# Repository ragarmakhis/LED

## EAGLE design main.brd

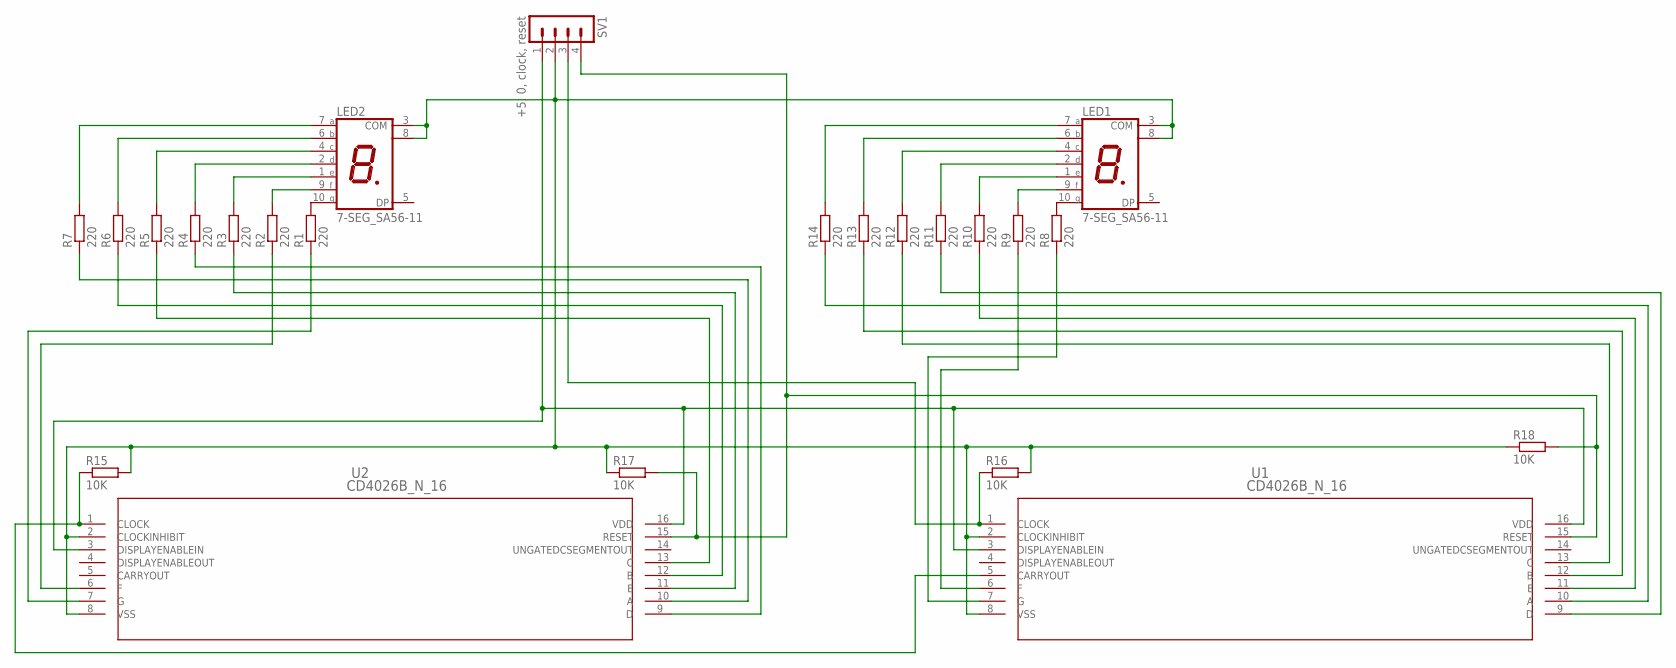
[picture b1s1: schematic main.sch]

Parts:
LED1, LED2: 7-SEG_SA56-11; SA56-11
R1, R2, R3, R4, R5, R6, R7, R8, R9, R10, R11, R12, R13, R14: 220; R0805
R15, R16, R17, R18: 10K; R0805
SV1: +5, 0, clock, reset; MA04-1
U1, U2: CD4026B_N_16; N16

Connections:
unnamed: LED2.10 (G), R1.2
unnamed: LED2.9 (F), R2.2
unnamed: LED2.1 (E), R3.2
unnamed: LED2.2 (D), R4.2
unnamed: LED2.4 (C), R5.2
unnamed: LED2.6 (B), R6.2
unnamed: LED2.7 (A), R7.2
unnamed: SV1.1, U1.3 (DISPLAYENABLEIN), U1.16 (VDD), U2.3 (DISPLAYENABLEIN), U2.16 (VDD)
unnamed: LED1.3 (COM), LED1.8 (COM), LED2.3 (COM), LED2.8 (COM), R15.2, R16.2, R17.1, R18.1, SV1.2, U1.2 (CLOCKINHIBIT), U1.8 (VSS), U2.2 (CLOCKINHIBIT), U2.8 (VSS)
unnamed: LED1.10 (G), R8.2
unnamed: LED1.9 (F), R9.2
unnamed: LED1.1 (E), R10.2
unnamed: LED1.2 (D), R11.2
unnamed: LED1.4 (C), R12.2
unnamed: LED1.6 (B), R13.2
unnamed: LED1.7 (A), R14.2
unnamed: R16.1, SV1.3, U1.1 (CLOCK)
unnamed: R7.1, U2.10 (A)
unnamed: R6.1, U2.12 (B)
unnamed: R5.1, U2.13 (C)
unnamed: R4.1, U2.9 (D)
unnamed: R3.1, U2.11 (E)
unnamed: R2.1, U2.6 (F)
unnamed: R1.1, U2.7 (G)
unnamed: R17.2, R18.2, SV1.4, U1.15 (RESET), U2.15 (RESET)
unnamed: R15.1, U1.5 (CARRYOUT), U2.1 (CLOCK)
unnamed: R9.1, U1.6 (F)
unnamed: R8.1, U1.7 (G)
unnamed: R12.1, U1.13 (C)
unnamed: R13.1, U1.12 (B)
unnamed: R10.1, U1.11 (E)
unnamed: R14.1, U1.10 (A)
unnamed: R11.1, U1.9 (D)

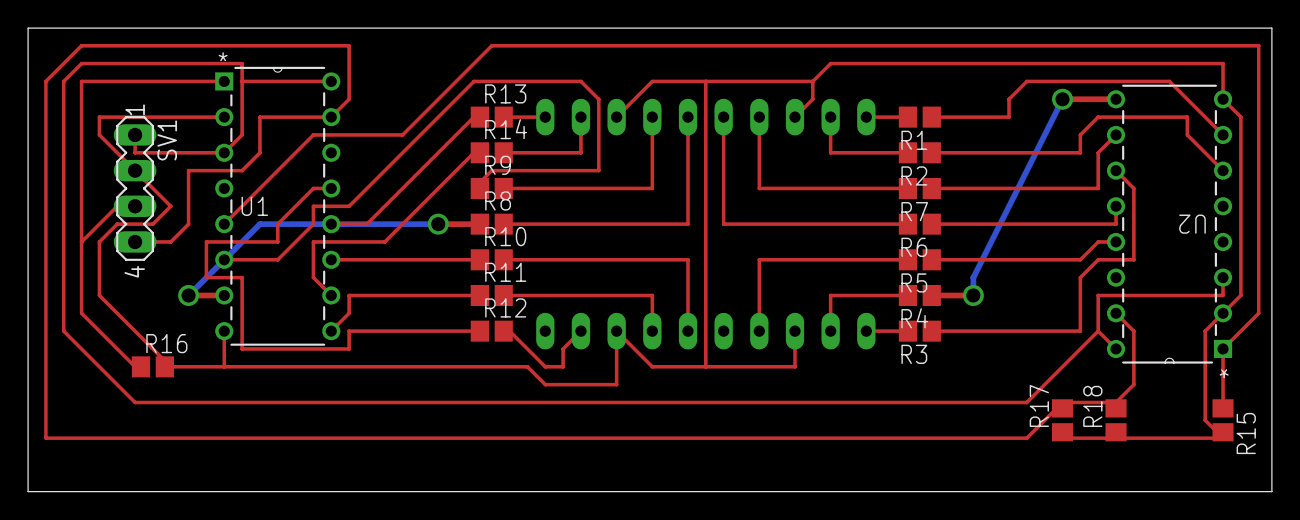
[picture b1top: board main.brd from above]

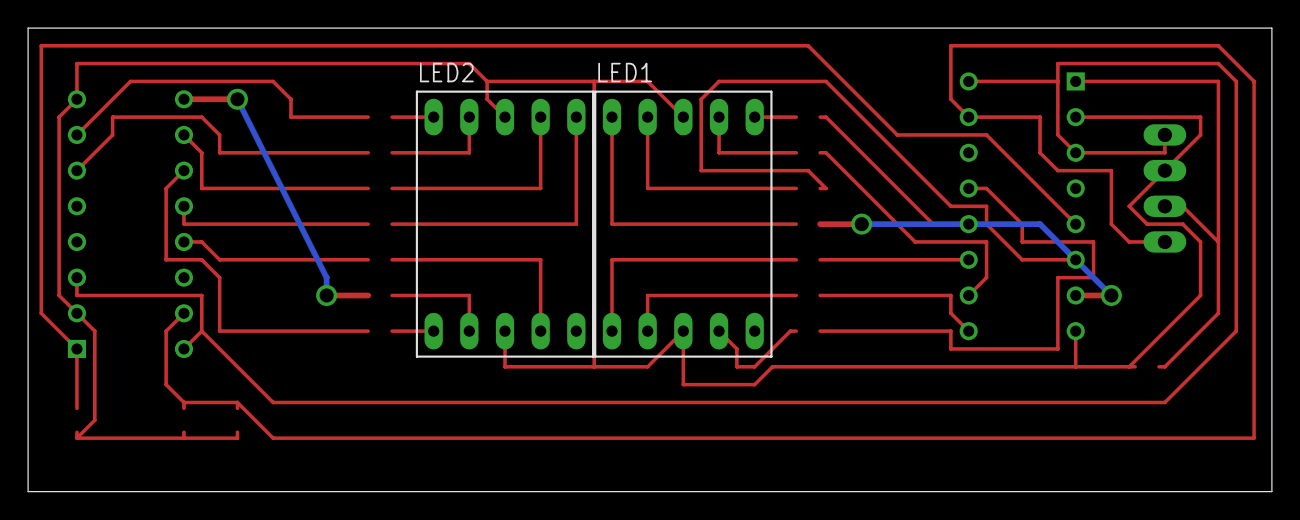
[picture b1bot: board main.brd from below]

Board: 2 copper layers, 88.6 x 33.0 mm, 23 parts (2 on the bottom side), 33 nets.

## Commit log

2012-12-21 first
2012-12-21 load
2012-12-28 Add v4 mirror drivers
2012-12-28 last
